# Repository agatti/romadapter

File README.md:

ROM Adapter board to be able to use AT28HC64B or 27256 OTP ROM chips in lieu of a 2364, to be fitted on a Commodore 64, Commodore 1541 Floppy Drive or other similar equipment.

Licensed under the CERN Open Hardware Licence Version 2 - Permissive, do whatever you want with this.

More information available in the schematics diagram.

Copyright 2021 Alessandro Gatti - frob.it

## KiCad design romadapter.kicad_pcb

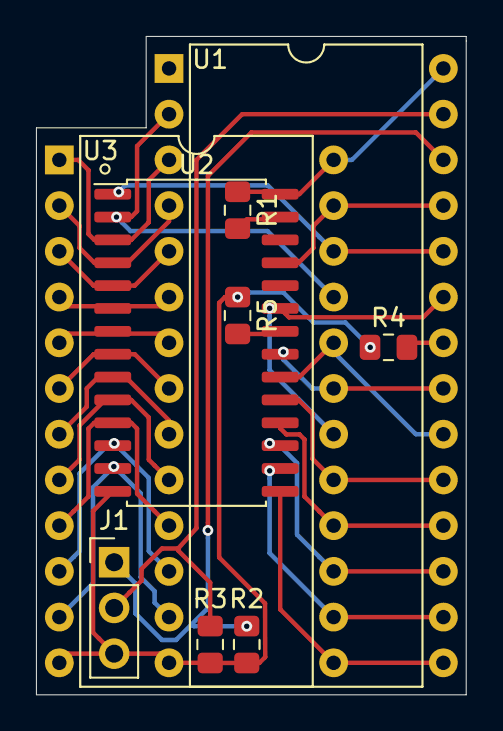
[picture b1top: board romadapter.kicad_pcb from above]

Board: 2 copper layers, 23.9 x 36.6 mm, 9 parts (0 on the bottom side), 29 nets.

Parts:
J1: EXT_SWITCH; PinHeader_1x03_P2.54mm_Vertical
R1, R2, R3, R4, R5: 4K7; R_0805_2012Metric_Pad1.15x1.40mm_HandSolder
U1: 27256; DIP-28_W15.24mm
U2: AT28HC64B; SOIC-28W_7.5x17.9mm_P1.27mm
U3: 2364; DIP-24_W15.24mm

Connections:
+5V: R1.1, U1.28, U2.28, U3.24
/A0: U1.10, U2.10, U3.8
/A1: U1.9, U2.9, U3.7
/A2: U1.8, U2.8, U3.6
/A3: U1.7, U2.7, U3.5
/A4: U1.6, U2.6, U3.4
/A5: U1.5, U2.5, U3.3
/A6: U1.4, U2.4, U3.2
/A7: U1.3, U2.3, U3.1
/A8: U1.25, U2.25, U3.23
/A9: U1.24, U2.1, U3.22
/A10: U1.21, U2.21, U3.19
/A11: U1.23, U2.23, U3.18
/A12: U1.2, U2.2, U3.21
/D0: U1.11, U2.11, U3.9
/D1: U1.12, U2.12, U3.10
/D2: U1.13, U2.13, U3.11
/D3: U1.15, U2.15, U3.13
/D4: U1.16, U2.16, U3.14
/D5: U1.17, U2.17, U3.15
/D6: U1.18, U2.18, U3.16
/D7: U1.19, U2.19, U3.17
/DIP_A13: J1.1, R2.2, U1.26
/DIP_A14: J1.2, R3.2, U1.27
/DIP_OE: R4.2, U1.22
/SOIC_OE: R5.2, U2.22
/SOIC_WE: R1.2, U2.27
/~CS: U1.20, U2.20, U3.20
GND: J1.3, R2.1, R3.1, R4.1, R5.1, U1.14, U2.14, U3.12

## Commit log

2021-02-24 Initial import.
